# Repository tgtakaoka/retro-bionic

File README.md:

<div align="center">

# retro-bionic

**Run real vintage CPUs on a modern Cortex-M7 — with a debugger, assembler and disassembler built in.**

</div>

## Contents

- [CPUs](docs/supported-cpus.md) — every target supported and planned, with the variants each detects
- [Hardware](docs/hardware.md) — the board stack, signal naming and the awkward chips
- [3.3 V base](docs/3v3-base.md) — planned second base board, its keying and what it unlocks
- [Debugger](docs/debugger.md) — full command reference
- [Build & run](docs/build.md) — toolchain, flashing, serial ports
- [Samples](docs/samples.md) — the programs and how to run them
- [CPU speed by an assembly-language Mandelbrot](docs/mandelbrot.md) — the benchmark's seconds per frame on each chip
- [Demos](docs/demos.md) — recorded terminal sessions, and what to watch for in them

## What is this?

Put a real MC6809, Z80, TMS9900 or CDP1802 into a ZIF socket and single-step it, one bus
cycle at a time, from a terminal on your desk.

**Bionic** runs *genuine* vintage processors — not emulations of them. A
[Teensy 4.1](https://www.pjrc.com/store/teensy41.html) is wired to every pin of the target
CPU and drives the whole system around it: the clock, every bus cycle, and the memory and
peripherals the chip thinks it is talking to. One firmware image — about 470 kB including
every assembler, disassembler and debugger — covers all **57 supported targets**, and the
board tells the controller which one it is.

<div align="center">

</div>

The hardware is two boards:

1. **Base** — the Teensy 4.1, five TXS0108E level shifters for 3.3 V ↔ 5 V translation, data
   bus holders, the 48-pin ZIF socket and the HALT/RUN switch.
2. **CPU adapter** — one small board per processor, holding little more than the chip
   itself, its identity EEPROM and whatever power the part demands. The TMS9900 board, for
   example, generates its own +12 V and −5 V rails and a non-overlapping four-phase clock, and CPUs with
   large address spaces carry an address bus multiplexer.

The 48 signals crossing the connector are named `P10`–`P57`, and each CPU board maps them to
its own pinout in a small TOML file. See **[docs/hardware.md](docs/hardware.md)**.

## Debugger features

- **Single-step a physical CPU** and print every bus cycle it performed (`S`).
- **Live disassembly** of the next instruction after each register dump, via
  [libasm](https://github.com/tgtakaoka/libasm).
- **Registers** read back by injecting instructions and capturing the resulting cycles —
  read and write them (`r`, `=`).
- **Breakpoints**, up to 4 plus one temporary for run-until-address (`B`, `b`, `g`).
- **Memory** dump and patch, separate program and data spaces for Harvard architectures
  (`d`, `p`, `m`, `M`), plus a write-protect area on targets that need one (`P`).
- **Upload** Intel HEX or Motorola S-record straight over the serial link (`U`).
- **Emulated peripherals** — MC6850 ACIA and i8251 USART — and on-chip serial ports of MCU
  targets bridged to your terminal (`I`).
- **Automatic board identification** from a UNI/O serial EEPROM, plus **runtime variant
  detection**: one 6502 board reports `MOS6502`, `G65SC02`, `R65C02`, `W65C02S` or
  `W65C816S` depending on which die actually responds.

<div align="center">

<br><em>A <a href="samples/tms9900/mandelbrot.cast">real TMS9900 session</a>: registers,
disassembly, single-stepping with the bus trace, then drawing the Mandelbrot set.</em>
</div>

## Supported CPUs

All 58 targets, grouped by vendor and architecture:

<table>
<thead>
<tr><th>Vendor</th><th>Architecture</th><th>Targets</th></tr>
</thead>
<tbody>
<tr><td rowspan="6">Motorola</td><td>6800</td><td>MC6800 <em>MB8861</em>, MC6801 <em>HD6301</em>, MC6802 <em>MB8870</em>, MC68HC11A, MC68HC11D</td></tr>
<tr><td>6805</td><td>MC146805E2, MC68HC05C0, MC68HC08AZ0</td></tr>
<tr><td>6809</td><td>MC6809 <em>HD6309</em>, MC6809E <em>HD6309E</em></td></tr>
<tr><td>68HC12</td><td>MC68HC12B, MC9S12D, MC9S12X</td></tr>
<tr><td>68HC16</td><td>MC68HC16Z</td></tr>
<tr><td>68000</td><td>MC68008P, MC68008FN, MC68000P <em>MC68010</em>, MC68000FN <em>MC68010</em></td></tr>
<tr><td>MOS Technology</td><td>6502</td><td>MOS6502 <em>G65SC02, R65C02, W65C02S, W65C816S</em></td></tr>
<tr><td rowspan="6">Zilog</td><td>Z80</td><td>Z80, NSC800, KL5C80A12</td></tr>
<tr><td>Z180</td><td>Z180, HD64180S</td></tr>
<tr><td>Z280</td><td>Z280</td></tr>
<tr><td>Z380</td><td>Z380</td></tr>
<tr><td>Z8000</td><td>Z8001, Z8002</td></tr>
<tr><td>Z8</td><td>Z86C91, Z88C00</td></tr>
<tr><td rowspan="5">Intel</td><td>MCS-48</td><td>P8039 <em>MSM80C39</em></td></tr>
<tr><td>MCS-51</td><td>P8051 <em>P80C51</em></td></tr>
<tr><td>MCS-80/85</td><td>P8080, P8085</td></tr>
<tr><td>x86</td><td>P8086 <em>P8088, V30, V20</em>, D8087</td></tr>
<tr><td>MCS-96</td><td>P8095BH, N8097BH, S80C196KC, S80296SA</td></tr>
<tr><td rowspan="4">Texas Instruments</td><td>TMS9900</td><td>TMS9900, TMS9980, TMS9981, TMS9995, TMS99105 <em>TMS99110</em></td></tr>
<tr><td>TMS7000</td><td>TMS7000 <em>TMS7001, TMS7001NL4, TMS7002, TMS70C00, TMS70C02</em></td></tr>
<tr><td>TMS370</td><td>TMS370Cx5x</td></tr>
<tr><td>TMS320</td><td>TMS320C15</td></tr>
<tr><td rowspan="2">DEC</td><td>PDP-8</td><td>IM6100, HD6120</td></tr>
<tr><td>PDP-11</td><td>DCT11, DCJ11</td></tr>
<tr><td>RCA</td><td>COSMAC</td><td>CDP1802 <em>CDP1804A</em></td></tr>
<tr><td>Fairchild</td><td>F8</td><td>F3850</td></tr>
<tr><td rowspan="2">National</td><td>SC/MP II</td><td>INS8060</td></tr>
<tr><td>SC/MP III</td><td>INS8070</td></tr>
<tr><td>Signetics</td><td>2650</td><td>SCN2650</td></tr>
<tr><td>Toshiba</td><td>TLCS-90</td><td>TMP90C802</td></tr>
<tr><td>Hitachi</td><td>H16</td><td>HD641016</td></tr>
<tr><td>Panafacom</td><td>MN1610</td><td>MN1613 <em>MN1613A</em></td></tr>
<tr><td>General Instrument</td><td>CP1600</td><td>CP1610</td></tr>
</tbody>
</table>

Targets in *italics* are variants the firmware identifies at runtime, by executing
instructions that behave differently on each die — not by anything written on the board.

See **[docs/supported-cpus.md](docs/supported-cpus.md)** for the full table, including the
CPUs still to be supported.

## Repository layout

| Path | Contents |
|---|---|
| [`debugger/`](debugger) | Teensy 4.1 firmware — shared framework plus 30 per-family back ends |
| [`schematics/`](schematics) | KiCad projects: base, mezzanine, PLCC adapter and 54 CPU adapter boards, with gerbers and PDFs |
| [`pinout/`](pinout) | Pin-map definitions consumed by [dip](https://github.com/tgtakaoka/dip) |
| [`samples/`](samples) | Test programs — Mandelbrot, arithmetic suites, serial echo — ported to every CPU |
| [`scripts/`](scripts) | Bench control, regression, cycle recording and timing scripts, and the PlatformIO `compile_commands.json` helper |

## Related projects

| Project | Role |
|---|---|
| [**libasm**](https://github.com/tgtakaoka/libasm) | The assembler and disassembler engine — 41 architectures, 119 CPU variants, small enough to run on an AVR |
| [**libcli**](https://github.com/tgtakaoka/libcli) | The serial command-line front end the debugger is built on |
| [**dip**](https://github.com/tgtakaoka/dip) | Draws the pinout diagrams from the TOML files in [`pinout/`](pinout) |

## Resources

- **Recorded sessions** — [asciinema.org/~tgtakaoka](https://asciinema.org/~tgtakaoka)
- **Progress log** — [Bluesky](https://bsky.app/profile/tgtakaoka.bsky.social) ·
  [X](https://x.com/tgtakaoka)

## License

Licensed under the [Apache License, Version 2.0](LICENSE.md).

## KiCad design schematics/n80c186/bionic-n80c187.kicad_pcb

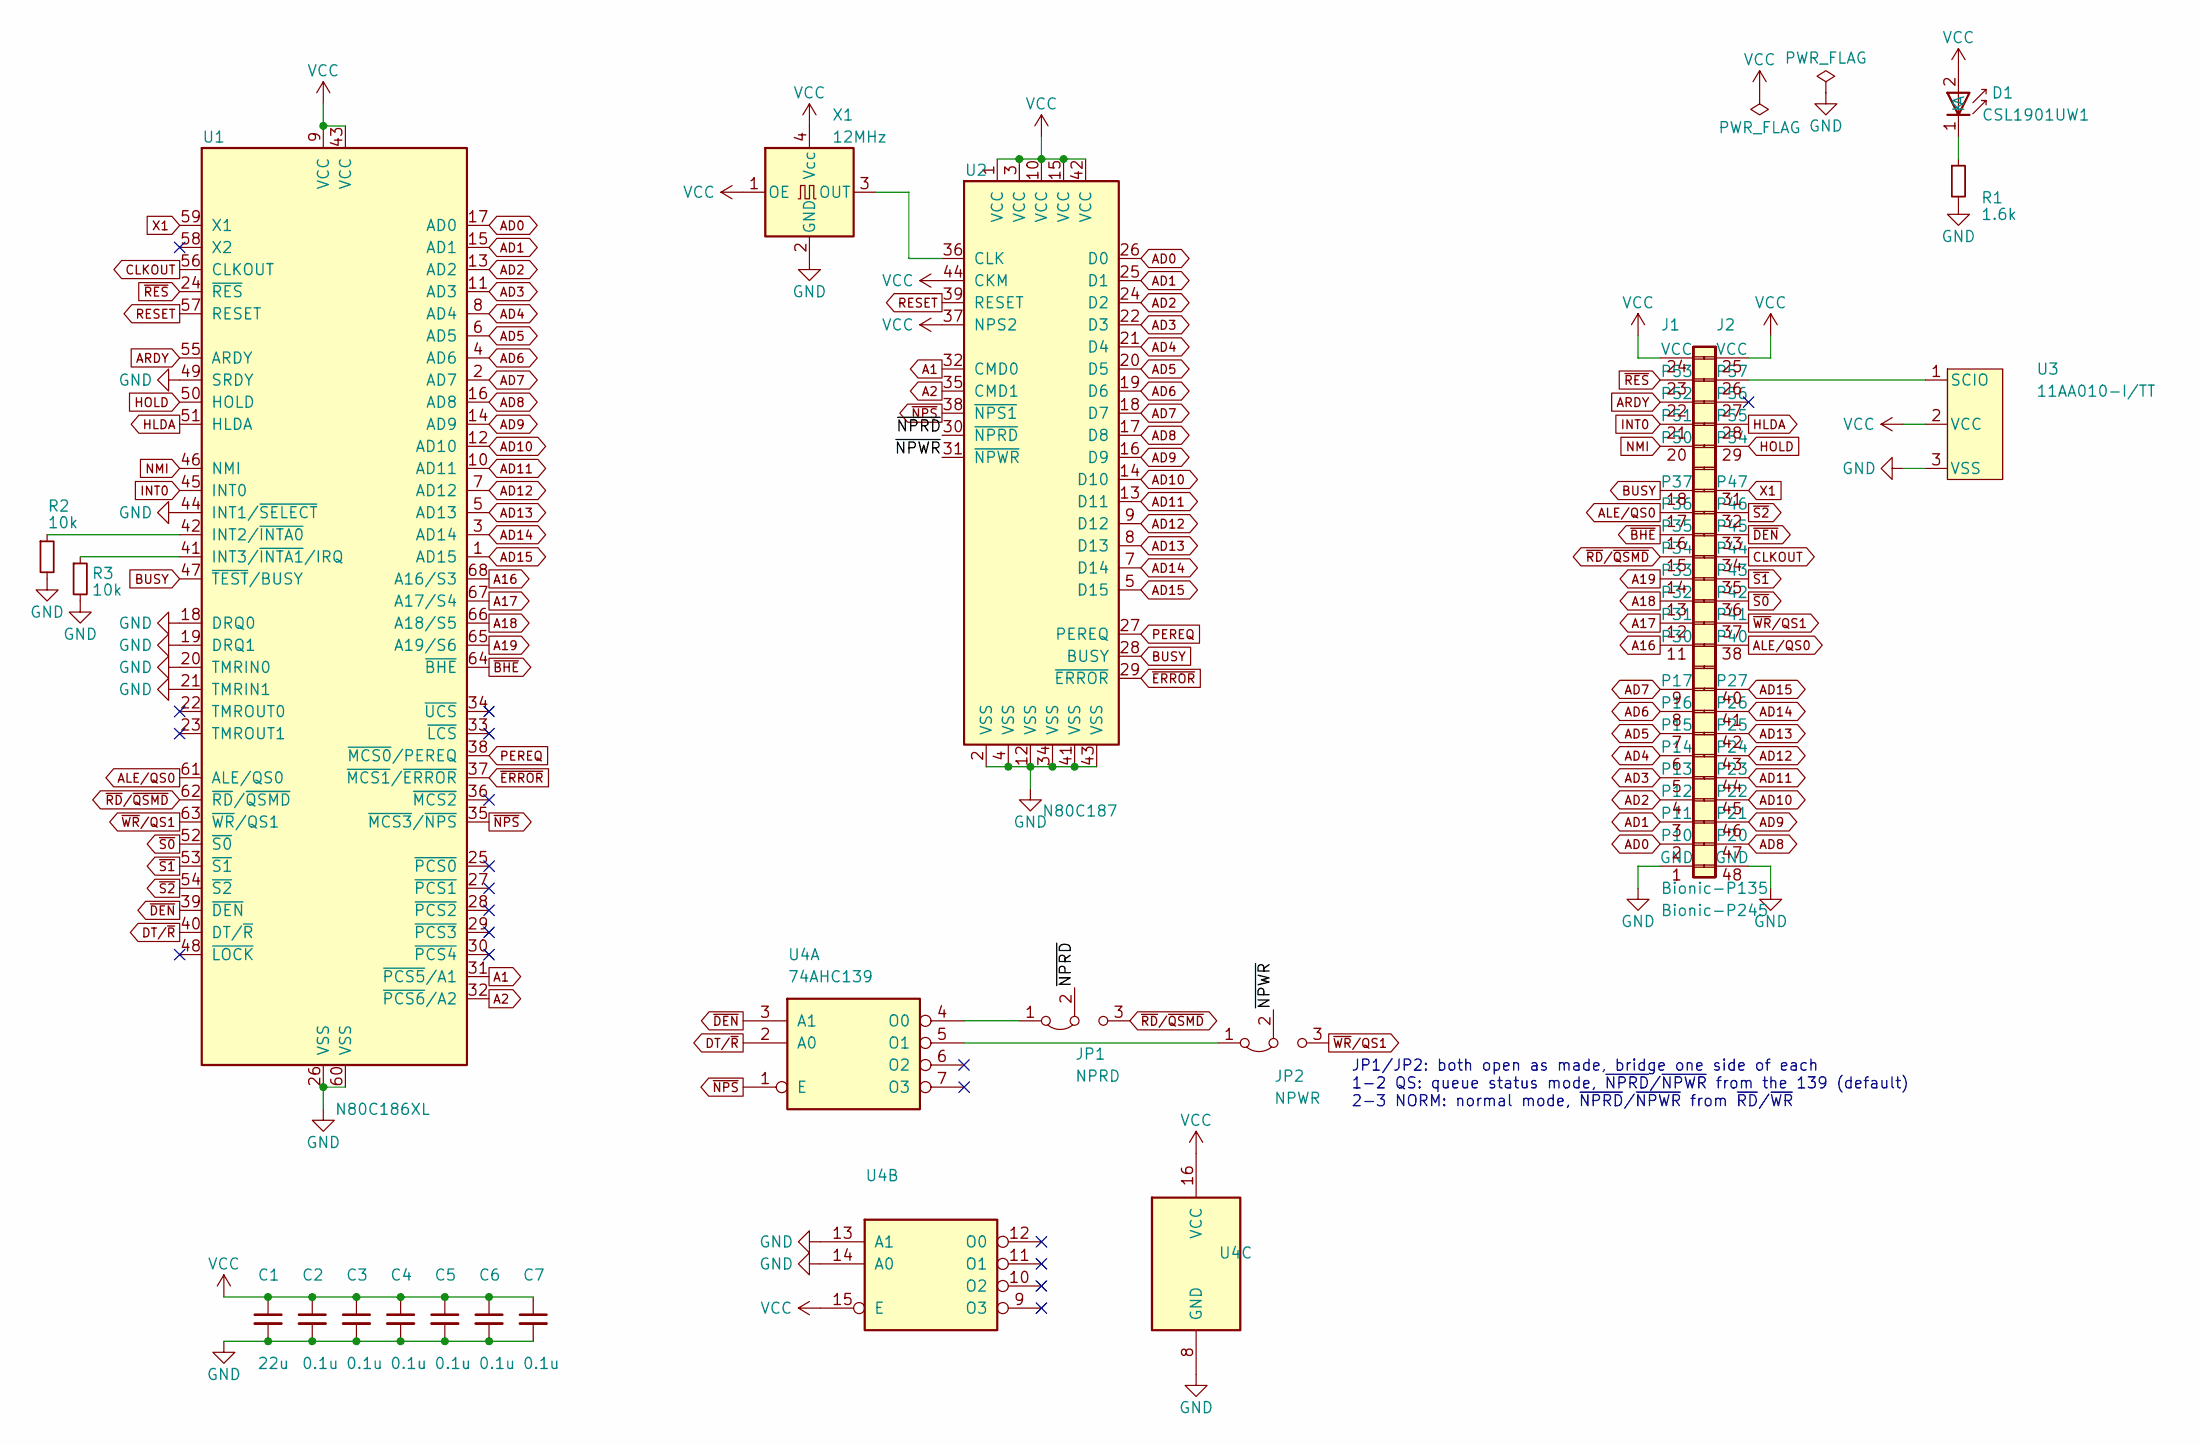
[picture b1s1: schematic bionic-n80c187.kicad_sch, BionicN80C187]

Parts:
C1: 22u; C_0603_1608Metric_Pad1.08x0.95mm_HandSolder
C2, C3, C4, C5, C6, C7: 0.1u; C_0603_1608Metric_Pad1.08x0.95mm_HandSolder
D1: CSL1901UW1; LED_CSL1901UW1_ROM-M
J1: Bionic-P135; Bionic-P135_SMT
J2: Bionic-P245; Bionic-P245_SMT
JP1: NPRD; SolderJumper-3_P2.0mm_Open_TrianglePad1.0x1.5mm_NumberLabels
JP2: NPWR; SolderJumper-3_P2.0mm_Open_TrianglePad1.0x1.5mm_NumberLabels
R1: 1.6k; R_0603_1608Metric_Pad0.98x0.95mm_HandSolder
R2, R3: 10k; R_0603_1608Metric_Pad0.98x0.95mm_HandSolder
U1: N80C186XL; PLCC-68_SMD-Socket_Intel
U2: N80C187; PLCC-44_SMD-Socket
U3: 11AA010-I/TT; SOT-23_MC_MCH-M
U4: 74AHC139; TSSOP-16_4.4x5mm_P0.65mm
X1: 12MHz; SX3M_3.2x2.5mm_HandSoldering

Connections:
/~NPRD: JP1.2 (C), U2.30 (~NPRD)
/~NPWR: JP2.2 (C), U2.31 (~NPWR)
A1: U1.31 (~PCS5/A1), U2.32 (CMD0)
A2: U1.32 (~PCS6/A2), U2.35 (CMD1)
A16: J1.11 (P30), U1.68 (A16/S3)
A17: J1.12 (P31), U1.67 (A17/S4)
A18: J1.13 (P32), U1.66 (A18/S5)
A19: J1.14 (P33), U1.65 (A19/S6)
AD0: J1.2 (P10), U1.17 (AD0), U2.26 (D0)
AD1: J1.3 (P11), U1.15 (AD1), U2.25 (D1)
AD2: J1.4 (P12), U1.13 (AD2), U2.24 (D2)
AD3: J1.5 (P13), U1.11 (AD3), U2.22 (D3)
AD4: J1.6 (P14), U1.8 (AD4), U2.21 (D4)
AD5: J1.7 (P15), U1.6 (AD5), U2.20 (D5)
AD6: J1.8 (P16), U1.4 (AD6), U2.19 (D6)
AD7: J1.9 (P17), U1.2 (AD7), U2.18 (D7)
AD8: J2.47 (P20), U1.16 (AD8), U2.17 (D8)
AD9: J2.46 (P21), U1.14 (AD9), U2.16 (D9)
AD10: J2.45 (P22), U1.12 (AD10), U2.14 (D10)
AD11: J2.44 (P23), U1.10 (AD11), U2.13 (D11)
AD12: J2.43 (P24), U1.7 (AD12), U2.9 (D12)
AD13: J2.42 (P25), U1.5 (AD13), U2.8 (D13)
AD14: J2.41 (P26), U1.3 (AD14), U2.7 (D14)
AD15: J2.40 (P27), U1.1 (AD15), U2.5 (D15)
ALE/QS0: J1.17 (P36), J2.38 (P40), U1.61 (ALE/QS0)
ARDY: J1.22 (P52), U1.55 (ARDY)
BUSY: J1.18 (P37), U1.47 (~TEST/BUSY), U2.28 (BUSY)
CLKOUT: J2.34 (P44), U1.56 (CLKOUT)
DT/~R: U1.40 (DT/~R), U4.2 (A0)
GND: C1.2, C2.2, C3.2, C4.2, C5.2, C6.2, C7.2, J1.1 (GND), J2.48 (GND), R1.2, R2.2, R3.2, U1.18 (DRQ0), U1.19 (DRQ1), U1.20 (TMRIN0), U1.21 (TMRIN1), U1.26 (VSS), U1.44 (INT1/~SELECT), U1.49 (SRDY), U1.60 (VSS), U2.2 (VSS), U2.4 (VSS), U2.12 (VSS), U2.34 (VSS), U2.41 (VSS), U2.43 (VSS), U3.3 (VSS), U4.8 (GND), U4.13 (A1), U4.14 (A0), X1.2 (GND)
HLDA: J2.28 (P55), U1.51 (HLDA)
HOLD: J2.29 (P54), U1.50 (HOLD)
INT0: J1.21 (P51), U1.45 (INT0)
NMI: J1.20 (P50), U1.46 (NMI)
unnamed: D1.1 (K), R1.1
unnamed: J2.26 (P57), U3.1 (SCIO)
unnamed: JP1.1 (A), U4.4 (O0)
unnamed: JP2.1 (A), U4.5 (O1)
unnamed: R2.1, U1.42 (INT2/~INTA0)
unnamed: R3.1, U1.41 (INT3/~INTA1/IRQ)
unnamed: U2.36 (CLK), X1.3 (OUT)
PEREQ: U1.38 (~MCS0/PEREQ), U2.27 (PEREQ)
RESET: U1.57 (RESET), U2.39 (RESET)
VCC: C1.1, C2.1, C3.1, C4.1, C5.1, C6.1, C7.1, D1.2 (A), J1.24 (VCC), J2.25 (VCC), U1.9 (VCC), U1.43 (VCC), U2.1 (VCC), U2.3 (VCC), U2.10 (VCC), U2.15 (VCC), U2.37 (NPS2), U2.42 (VCC), U2.44 (CKM), U3.2 (VCC), U4.15 (E), U4.16 (VCC), X1.1 (OE), X1.4 (Vcc)
X1: J2.31 (P47), U1.59 (X1)
~BHE: J1.16 (P35), U1.64 (~BHE)
~DEN: J2.33 (P45), U1.39 (~DEN), U4.3 (A1)
~ERROR: U1.37 (~MCS1/~ERROR), U2.29 (~ERROR)
~NPS: U1.35 (~MCS3/~NPS), U2.38 (~NPS1), U4.1 (E)
~RD/~QSMD: J1.15 (P34), JP1.3 (B), U1.62 (~RD/~QSMD)
~RES: J1.23 (P53), U1.24 (~RES)
~S0: J2.36 (P42), U1.52 (~S0)
~S1: J2.35 (P43), U1.53 (~S1)
~S2: J2.32 (P46), U1.54 (~S2)
~WR/QS1: J2.37 (P41), JP2.3 (B), U1.63 (~WR/QS1)

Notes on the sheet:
JP1/JP2: both open as made, bridge one side of each 1-2 QS: queue status mode, ~{NPRD}/~{NPWR} from the 139 (default) 2-3 NORM: normal mode, ~{NPRD}/~{NPWR} from ~{RD}/~{WR}

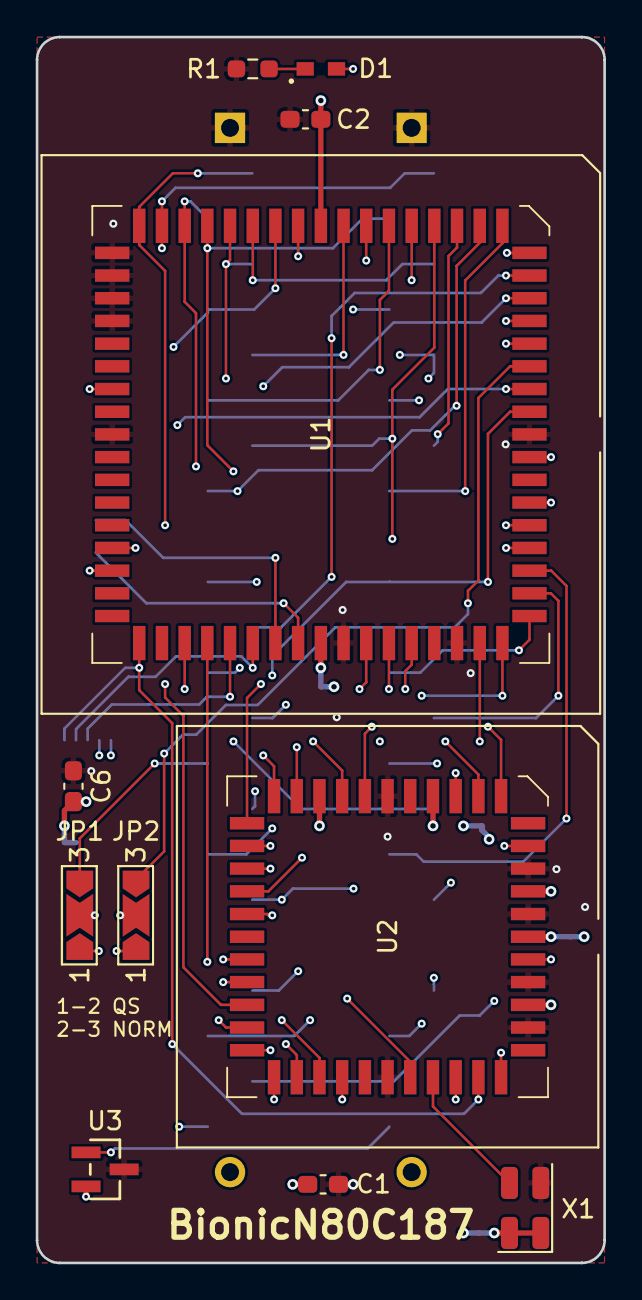
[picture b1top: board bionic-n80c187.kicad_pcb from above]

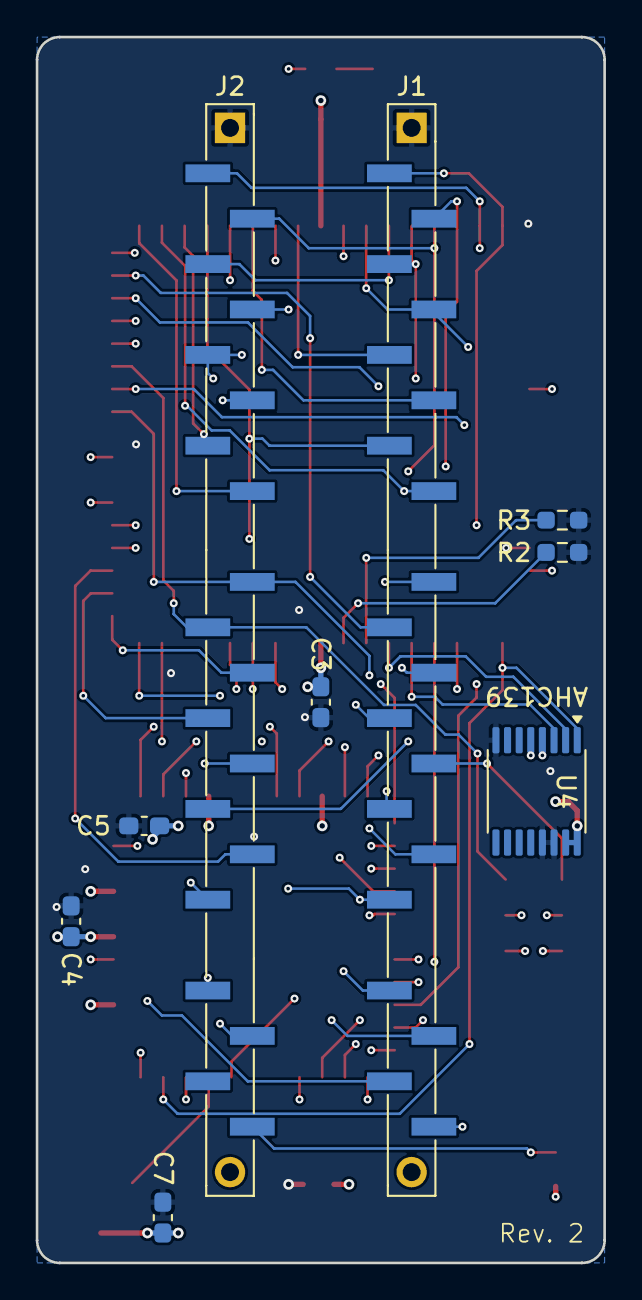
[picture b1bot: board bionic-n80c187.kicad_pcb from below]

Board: 4 copper layers, 31.7 x 68.6 mm, 20 parts (9 on the bottom side), 55 nets.

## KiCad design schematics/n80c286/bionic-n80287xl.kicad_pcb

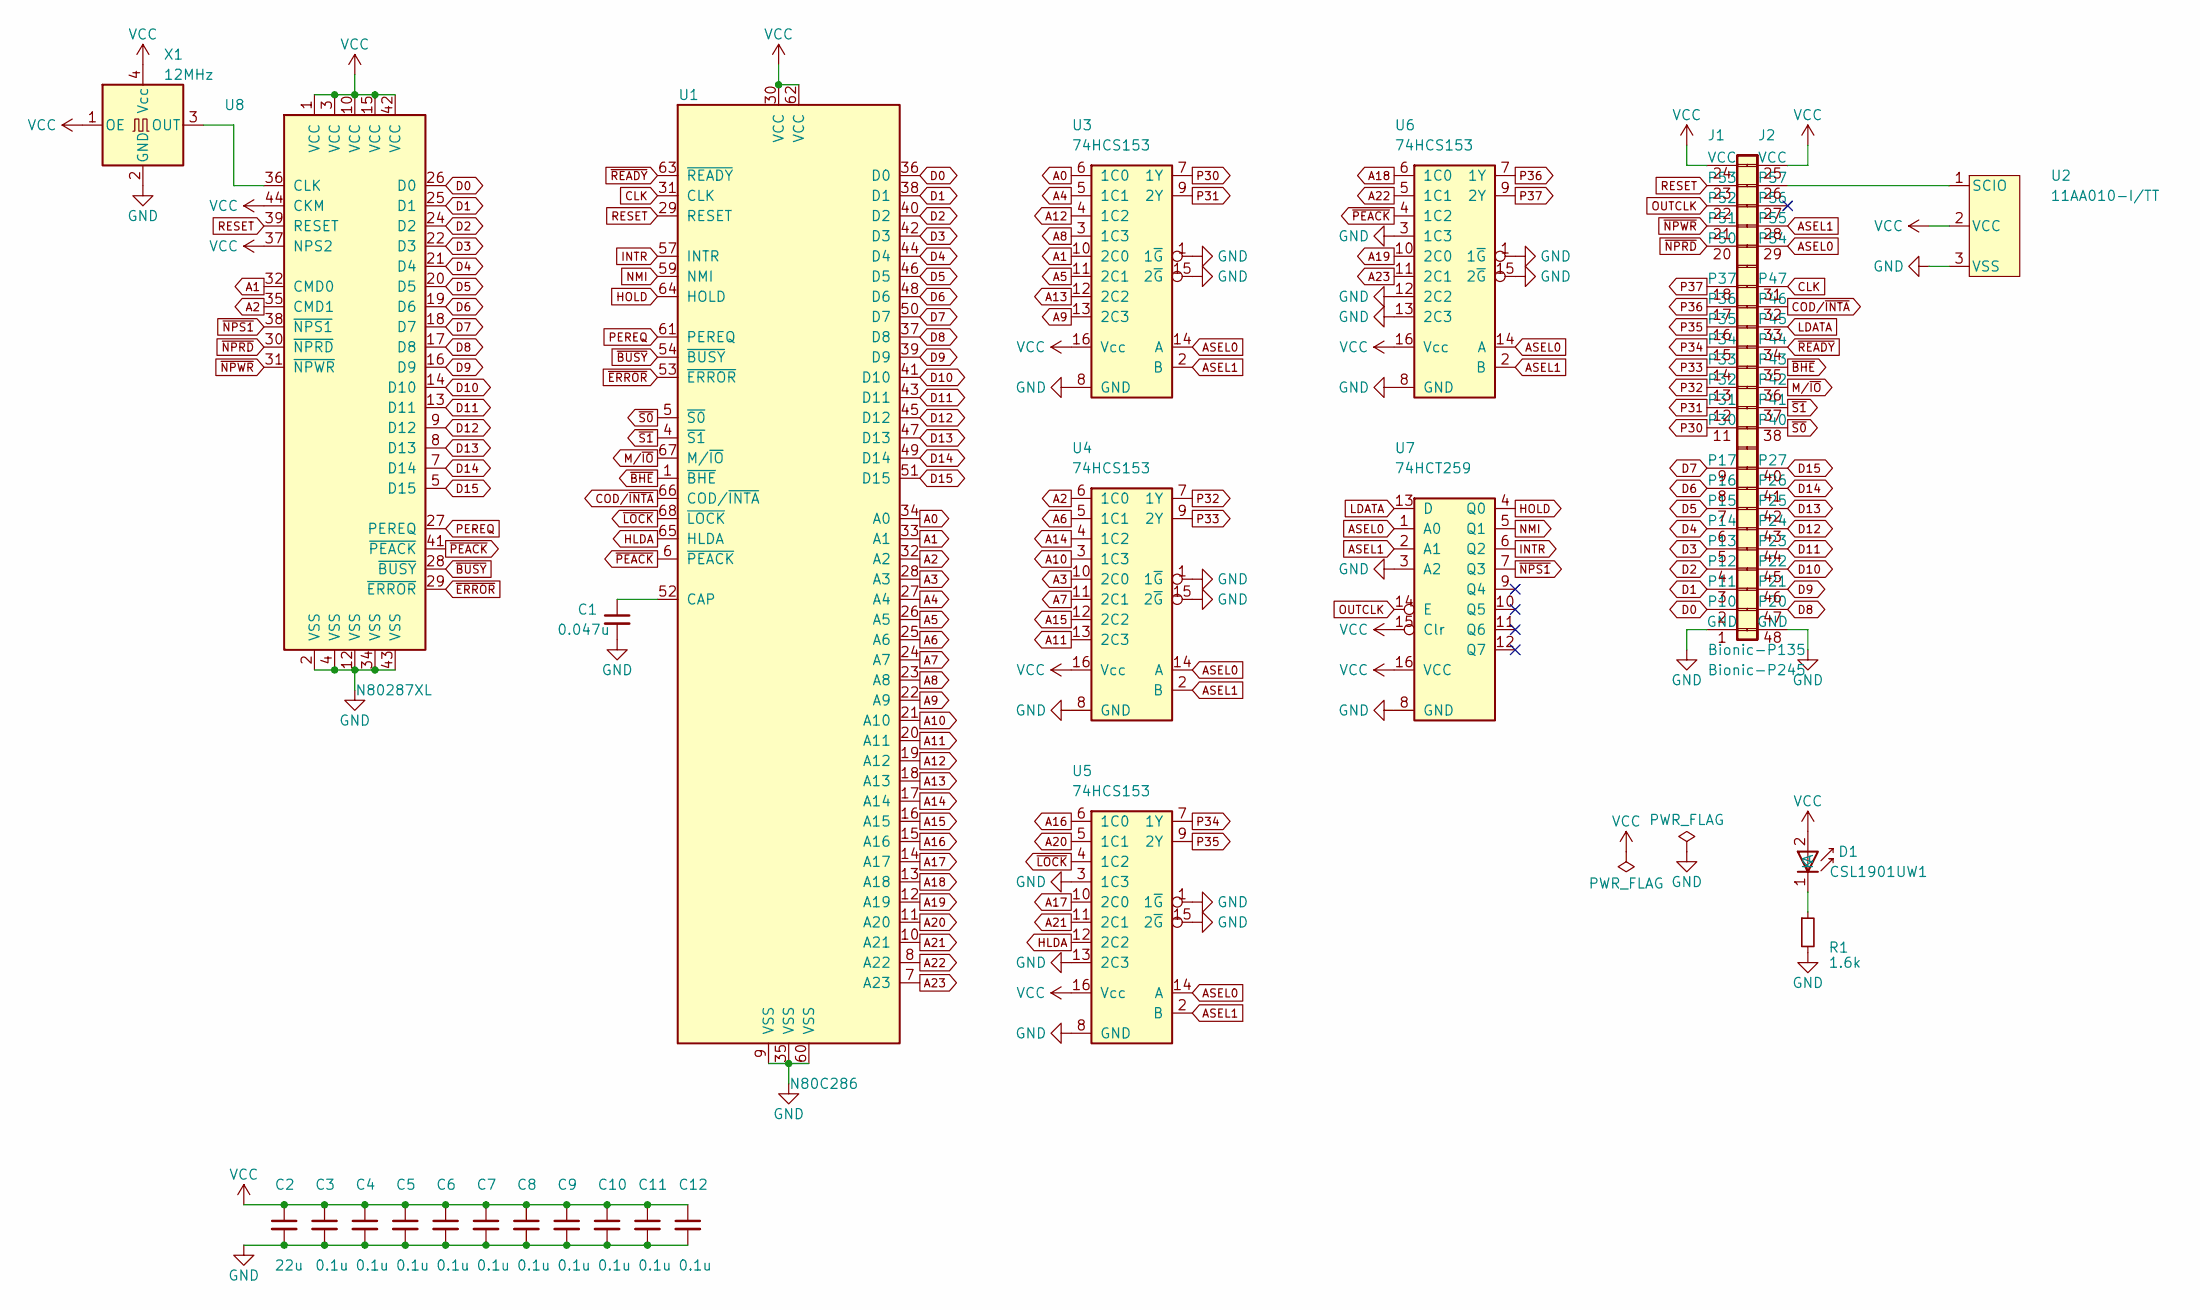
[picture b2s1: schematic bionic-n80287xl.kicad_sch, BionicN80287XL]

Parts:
C1: 0.047u; C_0603_1608Metric_Pad1.08x0.95mm_HandSolder
C2: 22u; C_0603_1608Metric_Pad1.08x0.95mm_HandSolder
C3, C4, C5, C6, C7, C8, C9, C10, C11, C12: 0.1u; C_0603_1608Metric_Pad1.08x0.95mm_HandSolder
D1: CSL1901UW1; LED_CSL1901UW1_ROM-M
J1: Bionic-P135; Bionic-P135_SMT
J2: Bionic-P245; Bionic-P245_SMT
R1: 1.6k; R_0603_1608Metric_Pad0.98x0.95mm_HandSolder
U1: N80C286; PLCC-68_SMD-Socket_Intel
U2: 11AA010-I/TT; SOT-23_MC_MCH-M
U3, U4, U5, U6: 74HCS153; PW16-M
U7: 74HCT259; TSSOP16_SOT403-1_NEX-M
U8: N80287XL; PLCC-44_SMD-Socket
X1: 12MHz; SX3M_3.2x2.5mm_HandSoldering

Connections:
A0: U1.34 (A0), U3.6 (1C0)
A1: U1.33 (A1), U3.10 (2C0), U8.32 (CMD0)
A2: U1.32 (A2), U4.6 (1C0), U8.35 (CMD1)
A3: U1.28 (A3), U4.10 (2C0)
A4: U1.27 (A4), U3.5 (1C1)
A5: U1.26 (A5), U3.11 (2C1)
A6: U1.25 (A6), U4.5 (1C1)
A7: U1.24 (A7), U4.11 (2C1)
A8: U1.23 (A8), U3.3 (1C3)
A9: U1.22 (A9), U3.13 (2C3)
A10: U1.21 (A10), U4.3 (1C3)
A11: U1.20 (A11), U4.13 (2C3)
A12: U1.19 (A12), U3.4 (1C2)
A13: U1.18 (A13), U3.12 (2C2)
A14: U1.17 (A14), U4.4 (1C2)
A15: U1.16 (A15), U4.12 (2C2)
A16: U1.15 (A16), U5.6 (1C0)
A17: U1.14 (A17), U5.10 (2C0)
A18: U1.13 (A18), U6.6 (1C0)
A19: U1.12 (A19), U6.10 (2C0)
A20: U1.11 (A20), U5.5 (1C1)
A21: U1.10 (A21), U5.11 (2C1)
A22: U1.8 (A22), U6.5 (1C1)
A23: U1.7 (A23), U6.11 (2C1)
ASEL0: J2.29 (P54), U3.14 (A), U4.14 (A), U5.14 (A), U6.14 (A), U7.1 (A0)
ASEL1: J2.28 (P55), U3.2 (B), U4.2 (B), U5.2 (B), U6.2 (B), U7.2 (A1)
CLK: J2.31 (P47), U1.31 (CLK)
COD/~INTA: J2.32 (P46), U1.66 (COD/~INTA)
D0: J1.2 (P10), U1.36 (D0), U8.26 (D0)
D1: J1.3 (P11), U1.38 (D1), U8.25 (D1)
D2: J1.4 (P12), U1.40 (D2), U8.24 (D2)
D3: J1.5 (P13), U1.42 (D3), U8.22 (D3)
D4: J1.6 (P14), U1.44 (D4), U8.21 (D4)
D5: J1.7 (P15), U1.46 (D5), U8.20 (D5)
D6: J1.8 (P16), U1.48 (D6), U8.19 (D6)
D7: J1.9 (P17), U1.50 (D7), U8.18 (D7)
D8: J2.47 (P20), U1.37 (D8), U8.17 (D8)
D9: J2.46 (P21), U1.39 (D9), U8.16 (D9)
D10: J2.45 (P22), U1.41 (D10), U8.14 (D10)
D11: J2.44 (P23), U1.43 (D11), U8.13 (D11)
D12: J2.43 (P24), U1.45 (D12), U8.9 (D12)
D13: J2.42 (P25), U1.47 (D13), U8.8 (D13)
D14: J2.41 (P26), U1.49 (D14), U8.7 (D14)
D15: J2.40 (P27), U1.51 (D15), U8.5 (D15)
GND: C1.2, C2.2, C3.2, C4.2, C5.2, C6.2, C7.2, C8.2, C9.2, C10.2, C11.2, C12.2, J1.1 (GND), J2.48 (GND), R1.2, U1.9 (VSS), U1.35 (VSS), U1.60 (VSS), U2.3 (VSS), U3.1 (1~G), U3.8 (GND), U3.15 (2~G), U4.1 (1~G), U4.8 (GND), U4.15 (2~G), U5.1 (1~G), U5.3 (1C3), U5.8 (GND), U5.13 (2C3), U5.15 (2~G), U6.1 (1~G), U6.3 (1C3), U6.8 (GND), U6.12 (2C2), U6.13 (2C3), U6.15 (2~G), U7.3 (A2), U7.8 (GND), U8.2 (VSS), U8.4 (VSS), U8.12 (VSS), U8.34 (VSS), U8.43 (VSS), X1.2 (GND)
HLDA: U1.65 (HLDA), U5.12 (2C2)
HOLD: U1.64 (HOLD), U7.4 (Q0)
INTR: U1.57 (INTR), U7.6 (Q2)
LDATA: J2.33 (P45), U7.13 (D)
M/~IO: J2.36 (P42), U1.67 (M/~IO)
NMI: U1.59 (NMI), U7.5 (Q1)
unnamed: D1.1 (K), R1.1
unnamed: J2.26 (P57), U2.1 (SCIO)
unnamed: C1.1, U1.52 (CAP)
unnamed: U8.36 (CLK), X1.3 (OUT)
OUTCLK: J1.22 (P52), U7.14 (E)
P30: J1.11 (P30), U3.7 (1Y)
P31: J1.12 (P31), U3.9 (2Y)
P32: J1.13 (P32), U4.7 (1Y)
P33: J1.14 (P33), U4.9 (2Y)
P34: J1.15 (P34), U5.7 (1Y)
P35: J1.16 (P35), U5.9 (2Y)
P36: J1.17 (P36), U6.7 (1Y)
P37: J1.18 (P37), U6.9 (2Y)
PEREQ: U1.61 (PEREQ), U8.27 (PEREQ)
RESET: J1.23 (P53), U1.29 (RESET), U8.39 (RESET)
VCC: C2.1, C3.1, C4.1, C5.1, C6.1, C7.1, C8.1, C9.1, C10.1, C11.1, C12.1, D1.2 (A), J1.24 (VCC), J2.25 (VCC), U1.30 (VCC), U1.62 (VCC), U2.2 (VCC), U3.16 (Vcc), U4.16 (Vcc), U5.16 (Vcc), U6.16 (Vcc), U7.15 (Clr), U7.16 (VCC), U8.1 (VCC), U8.3 (VCC), U8.10 (VCC), U8.15 (VCC), U8.37 (NPS2), U8.42 (VCC), U8.44 (CKM), X1.1 (OE), X1.4 (Vcc)
~BHE: J2.35 (P43), U1.1 (~BHE)
~BUSY: U1.54 (~BUSY), U8.28 (~BUSY)
~ERROR: U1.53 (~ERROR), U8.29 (~ERROR)
~LOCK: U1.68 (~LOCK), U5.4 (1C2)
~NPRD: J1.20 (P50), U8.30 (~NPRD)
~NPS1: U7.7 (Q3), U8.38 (~NPS1)
~NPWR: J1.21 (P51), U8.31 (~NPWR)
~PEACK: U1.6 (~PEACK), U6.4 (1C2), U8.41 (~PEACK)
~READY: J2.34 (P44), U1.63 (~READY)
~S0: J2.38 (P40), U1.5 (~S0)
~S1: J2.37 (P41), U1.4 (~S1)

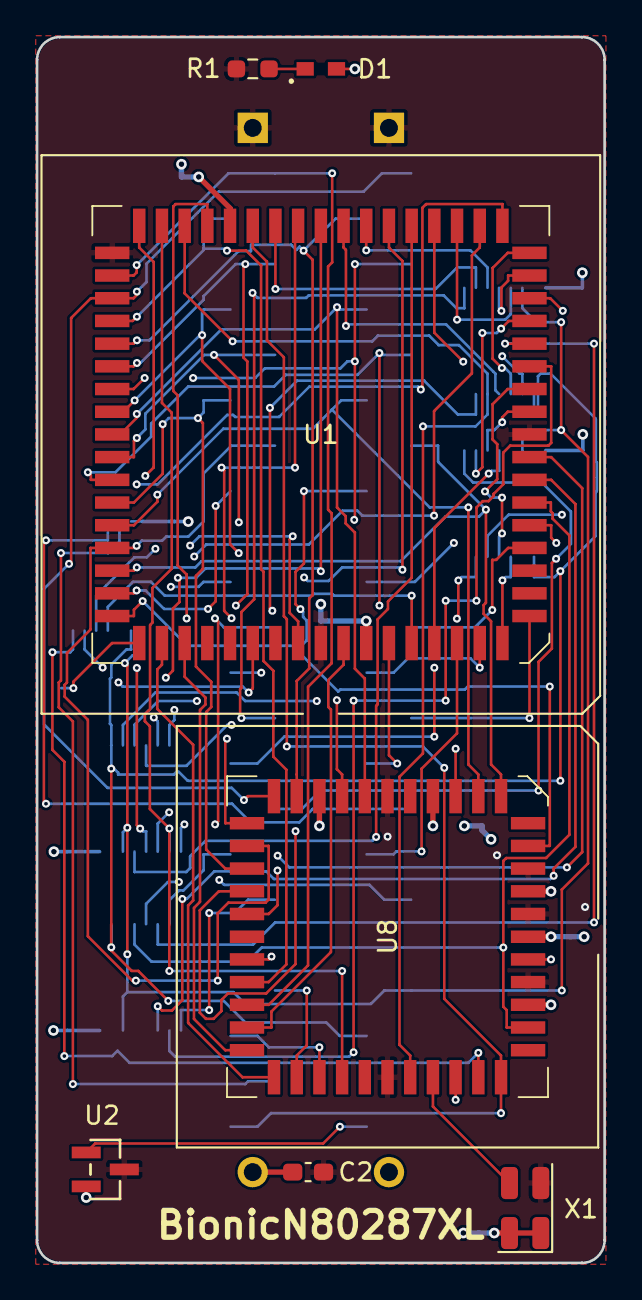
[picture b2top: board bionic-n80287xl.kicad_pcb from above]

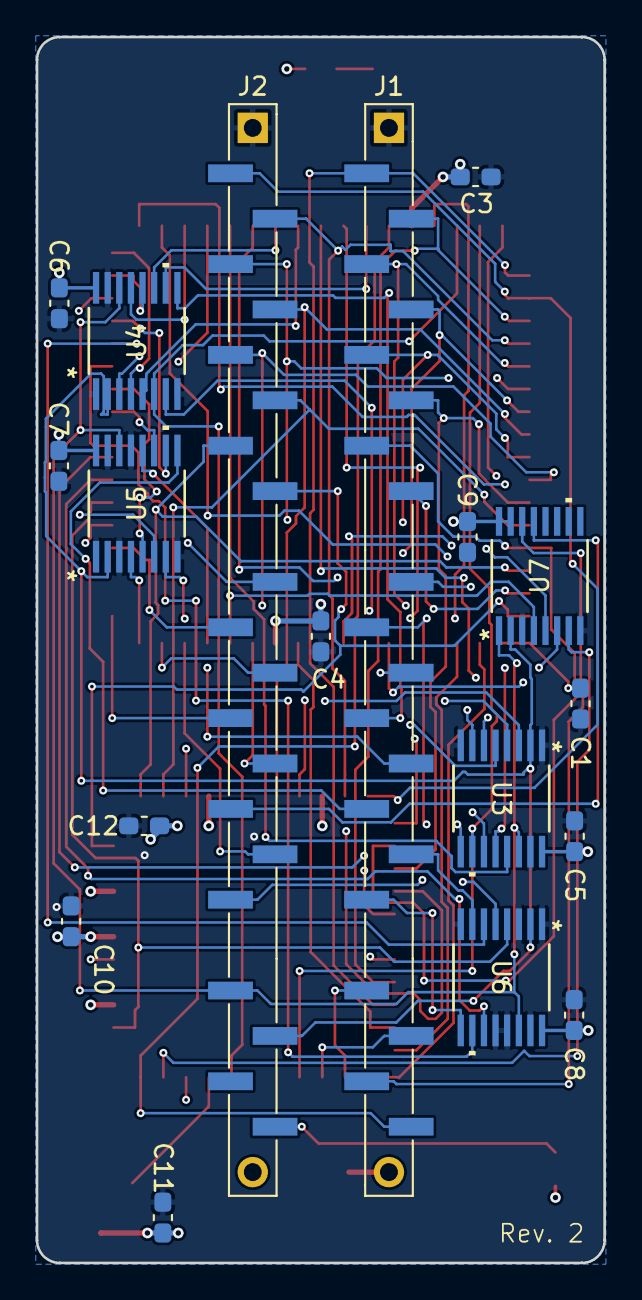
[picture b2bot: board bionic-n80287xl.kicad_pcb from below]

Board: 4 copper layers, 31.7 x 68.6 mm, 25 parts (18 on the bottom side), 78 nets.

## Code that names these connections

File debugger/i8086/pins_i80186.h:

#ifndef __PINS_I80186_H__
#define __PINS_I80186_H__

// The BionicN80C186 and BionicN80C187 boards (schematics/n80c186): an
// N80C186XL, with an N80C187 on the second, in queue status mode.
#include "pins_i8086_bus.h"
#define PIN_RDQSMD 8 /* P7.16 P34, held low: queue status mode */
#define PIN_BHE 7    /* P7.17 P35 */
#define PIN_ALE2 36  /* P7.18 P36, ALE/QS0's FlexIO3 copy */
#define PIN_TEST 37  /* P7.19 P37, the BionicN80C187 board's 80C187 BUSY */
#define BHE_BIT 17   /* #BHE in PORT_AH */
// QS0, QS1 and #S0-#S2 in one read of GPIO9.
#define PORT_CNTL 9  /* GPIO9 */
#define CNTL_gp 4    /* P9.04-P9.08 */
#define CNTL_gm 0x1F /* P9.04-P9.08 */
#define CNTL_vp 0
#define PIN_QS0 2      /* P9.04 P40, ALE in normal mode */
#define PIN_QS1 3      /* P9.05 P41, #WR in normal mode */
#define PIN_S0 4       /* P9.06 P42 */
#define PIN_S1 33      /* P9.07 P43 */
#define PIN_S2 5       /* P9.08 P46 */
#define PIN_CLKOUT 0   /* P6.03 P44 */
#define PIN_DEN 1      /* P6.02 P45 */
#define PIN_X1 29      /* P9.31 P47 */
#define PIN_NMI 6      /* P7.10 P50 */
#define PIN_INT0 9     /* P7.11 P51 */
#define PIN_ARDY 32    /* P7.12 P52 */
#define PIN_RES 28     /* P8.18 P53 */
#define PIN_HOLD 31    /* P8.22 P54 */
#define PIN_HLDA 30    /* P8.23 P55 */

#if defined(I80186_NORMAL_BUS)
#error "N80C186: the normal bus mode (ALE, #RD, #WR) is not written yet"
#endif

#include "pins_i8086_base.h"

namespace debugger {
namespace i8086 {

// The 80C186XL is static: the debugger toggles X1 itself, one edge at a
// time, and a cycle lasts as long as it takes to serve.
struct PinsI80186 final : PinsI8086Base {
    // |npx|: the BionicN80C187 board's 80C187 drives TEST/BUSY.
    PinsI80186(bool npx);

    // The CPU waits unclocked.
    void idle() override {}
#ifdef TUNE_CLOCK
    bool setClockInput(uint32_t hz) override;
#endif

    void assertInt(uint8_t name) override;
    void negateInt(uint8_t name) override;

private:
    // CLKOUT periods clocked, each with its queue status sample.
    uint32_t _clocks = 0;
    // GPIO9 as read after the latest rising edge of CLKOUT.
    uint32_t _p9;

    void resetPins() override;
    Signals *prepareCycle() override;
    Signals *completeCycle(Signals *s) override;
    void assertNmi() override;
    void negateNmi() override;
    void freezeQs() override;
    uint32_t clockCycles() const override { return 1; }
    void fall();
    void rise();
    // Whether |s| accesses the Peripheral Control Block, which the CPU
    // serves itself.
    bool pcb(const Signals *s) const;
    // Whether |s| accesses the 80C187.
    bool npx(const Signals *s) const;
    bool parkAtReset(Signals *s);
};

}  // namespace i8086
}  // namespace debugger
#endif /* __PINS_I80186_H__ */

// Local Variables:
// mode: c++
// c-basic-offset: 4
// tab-width: 4
// End:
// vim: set ft=cpp et ts=4 sw=4:

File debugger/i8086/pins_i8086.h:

#ifndef __PINS_I8086_H__
#define __PINS_I8086_H__

// The P8086 and D8087 boards (schematics/p8086), in maximum mode. The 8088
// and V20 have HIGH where the 8086 has #BHE.
#include "pins_i8086_bus.h"
// QS0, #S1, #S0 and #TEST share A16-A19's port.
#define PIN_QS0 8   /* P7.16 P34 */
#define PIN_S1 7    /* P7.17 P35 */
#define PIN_S0 36   /* P7.18 P36 */
#define PIN_TEST 37 /* P7.19 P37, the D8087 board's 8087 BUSY */
// #RD, #LOCK, QS1, #BHE and #S2 in one read of GPIO9; Signals keeps the
// strobes #S2-#S0 stand for in the same bits.
#define PORT_CNTL 9  /* GPIO9 */
#define CNTL_gp 4    /* P9.04-P9.08 */
#define CNTL_gm 0x1F /* P9.04-P9.08 */
#define CNTL_vp 0
#define PIN_RD 2     /* P9.04 P40 */
#define PIN_LOCK 3   /* P9.05 P41 */
#define PIN_QS1 4    /* P9.06 P42 */
#define PIN_BHE 33   /* P9.07 P43 */
#define PIN_S2 5     /* P9.08 P46 */
#define PIN_INT 0    /* P6.03 P44, the D8087 board's 8087 INT */
#define PIN_MNMX 1   /* P6.02 P45 */
#define PIN_CLK 29   /* P9.31 P47 */
#define PIN_NMI 6    /* P7.10 P50 */
#define PIN_INTR 9   /* P7.11 P51 */
#define PIN_READY 32 /* P7.12 P52 */
#define PIN_RESET 28 /* P8.18 P53 */
#define PIN_RQGT0 31 /* P8.22 P54, the CPU's and the 8087's */
#define PIN_RQGT1 30 /* P8.23 P55 */
// #S1 and #S0; #S2 is CNTL's.
#define PORT_S01 7 /* GPIO7 */
#define S01_gp 17  /* P7.17-P7.18 */
#define S01_gm 0x3 /* P7.17-P7.18 */
#define S01_vp 0   /* #S1, #S0 */

#include "pins_i8086_base.h"
#include "pwm_clock.h"

namespace debugger {
namespace i8086 {

// CLK free-runs from FlexPWM3, as the NMOS 8087 and the V20/V30 need, and
// the debugger holds each bus cycle in wait states with READY low.
struct PinsI8086 final : PinsI8086Base {
    // |fpu|: the D8087 board's 8087 shares the bus. Reset tells the 8088
    // and V20 from the 8086 and V30, and the NEC parts from Intel's.
    PinsI8086(bool fpu);

    // The clock runs on; READY holds the parked CPU.
    void idle() override;
#ifdef TUNE_CLOCK
    uint32_t clockInput() const override { return _clockInput; }
    bool setClockInput(uint32_t hz) override;
#endif

    void assertInt(uint8_t name) override;
    void negateInt(uint8_t name) override;

private:
    PwmClock<PIN_CLK> _clock;
#ifdef TUNE_CLOCK
    // CLK's rate, which K sets.
    uint32_t _clockInput;
#endif
    // The next cycle's T1, read ahead by completeCycle().
    Signals _latch;
    uint8_t _latchStatus;
    // When _latch showed its status, in CPU cycles.
    uint32_t _latchSeen;
    bool _latched = false;

    void resetPins() override;
    Signals *prepareCycle() override;
    Signals *completeCycle(Signals *s) override;
    void assertNmi() override;
    void negateNmi() override;
    void freezeQs() override;
    uint32_t clockCycles() const override;
    bool npxBusy() const override;
    bool latchCycle();
    void applyChipClock();
    // Parks at the reset fetch, |bus8| as the CPU showed it there; false
    // if the CPU's first cycle is not that fetch.
    bool parkAtReset(Signals *s, bool bus8);
};

}  // namespace i8086
}  // namespace debugger
#endif /* __PINS_I8086_H__ */

// Local Variables:
// mode: c++
// c-basic-offset: 4
// tab-width: 4
// End:
// vim: set ft=cpp et ts=4 sw=4:

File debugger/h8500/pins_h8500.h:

#ifndef __PINS_H8500_H__
#define __PINS_H8500_H__

// H8/510: D0-D15 on P10-P27.
#define PORT_D16 6    /* GPIO6 */
#define D16_gp 16     /* P6.16-P6.31 */
#define D16_gm 0xFFFF /* P6.16-P6.31 */
#define D16_vp 0      /* D0-D15 */
// H8/536: D0-D7 on P10-P17 and A0-A7 on P20-P27 share GPIO6, so its data
// bus drives the low half only.
#define PORT_D8 6   /* GPIO6 */
#define D8_gp 16    /* P6.16-P6.23 */
#define D8_gm 0xFF  /* P6.16-P6.23 */
#define D8_vp 0     /* D0-D7 */
#define PORT_AL 6   /* GPIO6 */
#define AL_gp 24    /* P6.24-P6.31 */
#define AL_gm 0xFF  /* P6.24-P6.31 */
#define AL_vp 0     /* A0-A7 */
#define PIN_D0 19   /* P6.16 */
#define PIN_D1 18   /* P6.17 */
#define PIN_D2 14   /* P6.18 */
#define PIN_D3 15   /* P6.19 */
#define PIN_D4 40   /* P6.20 */
#define PIN_D5 41   /* P6.21 */
#define PIN_D6 17   /* P6.22 */
#define PIN_D7 16   /* P6.23 */
#define PIN_D8 22   /* P6.24, the H8/536's A0 */
#define PIN_D9 23   /* P6.25 */
#define PIN_D10 20  /* P6.26 */
#define PIN_D11 21  /* P6.27 */
#define PIN_D12 38  /* P6.28 */
#define PIN_D13 39  /* P6.29 */
#define PIN_D14 26  /* P6.30 */
#define PIN_D15 27  /* P6.31, the H8/536's A7 */
// P30-P33 and P34-P37, one read of GPIO7. H8/510: two 74HCS153 and a
// 74AHCT157 selected by ASEL1:ASEL0 -- 00 A0-A3 and A16-A19, 01 A4-A7 and
// A20-A23, 11 A8-A11 and A20-A23, 10 A12-A15 and A16-A19. H8/536: a
// 74AHCT157 on P30-P33 selected by ASEL0, 0 A8-A11 and 1 A16-A19, and
// A12-A15 on P34-P37.
#define PORT_ADDR 7        /* GPIO7 */
#define ADDR_gp 0          /* P7.00-P7.03, P7.16-P7.19 */
#define ADDR_gm 0x000F000F /* P30-P33, P34-P37 */
#define ADDR_vp 0
#define PIN_AM0 10  /* P7.00 */
#define PIN_AM1 12  /* P7.01 */
#define PIN_AM2 11  /* P7.02 */
#define PIN_AM3 13  /* P7.03 */
#define PIN_AH0 8   /* P7.16 */
#define PIN_AH1 7   /* P7.17 */
#define PIN_AH2 36  /* P7.18 */
#define PIN_AH3 37  /* P7.19 */
// The strobes and the system clock ø, one read of GPIO9.
#define PIN_AS 2      /* P9.04 */
#define PIN_RD 3      /* P9.05 */
#define PIN_HWR 4     /* P9.06, the H8/536's #WR */
#define PIN_LWR 33    /* P9.07, open on the H8/536 */
#define PIN_PHI 5     /* P9.08 */
#define PORT_CNTL 9   /* GPIO9 */
#define CNTL_gp 4     /* P9.04-P9.08 */
#define CNTL_gm 0x1F  /* P9.04-P9.08 */
#define CNTL_vp 0
#define PIN_EXTAL 29  /* P9.31 */
#define PIN_IRQ0 6    /* P7.10 */
#define PIN_NMI 9     /* P7.11 */
#define PIN_WAIT 32   /* P7.12 */
#define PIN_RES 28    /* P8.18 */
#define PIN_ASEL0 31  /* P8.22 */
#define PIN_ASEL1 30  /* P8.23, open on the H8/536 */

#include "chip_h8500.h"
#include "pins.h"
#include "pwm_clock.h"
#include "regs_h8500.h"
#include "signals_h8500.h"

namespace debugger {
namespace h8500 {

struct PinsH8500 final : Pins {
    using Clock = PwmClock<PIN_EXTAL>;

    PinsH8500(const ChipH8500 &chip);

    // EXTAL runs free and the CPU waits in Tw: nothing to clock.
    void idle() override {}
    bool step(bool show) override;
    void run() override;

    void printCycles() override;
    uint32_t clockInput() const override { return _clockInput; }
    bool setClockInput(uint32_t hz) override;
    void assertInt(uint8_t name) override;
    void negateInt(uint8_t name) override;
    void setBreakInst(uint32_t addr) const override;

    const ChipH8500 &chip() const { return _chip; }
    uint32_t wrap(uint32_t addr) const { return addr & _chip.addrMask; }

    // Where an injected sequence leaves off: back at its own origin, or --
    // given as a plain address -- the target of the jump it ends with.
    static constexpr uint32_t EXIT_ORG = UINT32_MAX;

    // Run |inst| on the parked CPU: its reads inside the window are fed
    // from |inst| by address, the prefetch just past it gets NOPs, other
    // reads come from memory, and every write is captured, never stored.
    // The first |max| bytes written go to |buf| and their addresses to
    // |addrs|; the count captured is returned. |org| is where the CPU is
    // parked, and is advanced to where the sequence leaves off. Every
    // sequence ends in a taken jump.
    void execInst(const uint8_t *inst, uint_fast8_t len, uint32_t &org,
            uint32_t exit);
    uint_fast8_t captureWrites(const uint8_t *inst, uint_fast8_t len,
            uint8_t *buf, uint32_t *addrs, uint_fast8_t max, uint32_t &org,
            uint32_t exit);
    // Whether the last sequence ended anywhere but its exit.
    bool cutShort() const { return _cutShort; }
    // Complete the vector read the CPU is parked in with |handler|, and
    // park it again at the handler's first fetch.
    bool answerVector(uint32_t vecAddr, uint32_t handler);

private:
    const ChipH8500 &_chip;
    bool _cutShort = false;
    // EXTAL's rate, and the Teensy cycles in one of its clocks.
    uint32_t _clockInput;
    uint32_t _clockCycles;
    Clock _clock;
    void resetPins() override;
    void printBacktrace() override;
    bool setupBus();
    bool loop();
    uint32_t isException(const Signals *s, RegsH8500::Frame &frame,
            const Signals *&from) const;
    bool isBreak(const Signals *s, RegsH8500::Frame &frame,
            const Signals *&from) const;
    bool isHalt(const Signals *s, RegsH8500::Frame &frame,
            const Signals *&from) const;
    bool maskBreak(Signals *s, const RegsH8500::Frame &frame);
    bool isVector(const Signals *s, uint32_t vec) const;
    bool findFrame(const Signals *s, RegsH8500::Frame &frame,
            const Signals *&from) const;

    Signals *prepareCycle();
    // Gives up after |clocks| without #AS: the CPU sleeps or halted.
    Signals *prepareCycle(uint_fast16_t clocks);
    Signals *resumeCycle(uint32_t addr);
    Signals *completeCycle(Signals *s);
    void serveRead(Signals *s);
    void storeWrite(Signals *s);
    uint_fast8_t execute(const uint8_t *inst, uint_fast8_t len, uint8_t *buf,
            uint32_t *addrs, uint_fast8_t max, uint32_t &org, uint32_t exit);
    bool suspend(uint32_t org);
};

}  // namespace h8500
}  // namespace debugger
#endif /* __PINS_H8500_H__ */

// Local Variables:
// mode: c++
// c-basic-offset: 4
// tab-width: 4
// End:
// vim: set ft=cpp et ts=4 sw=4:

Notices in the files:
README.md:
License: Apache 2.0
